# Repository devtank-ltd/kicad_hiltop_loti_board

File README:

Copyright Devtank Ltd 2021.

This documentation describes Open Hardware and is Licensed under CERN-OHL-W v2.

You may redistribute and modify this documentation under the terms of the CERN-OHL-W v2 (https://cern.ch/cern-ohl). This documentation is distributed WITHOUT ANY EXPRESS OR IMPLIED WARRANTY, INCLUDING OF MERCHANTABILITY, SATISFACTORY QUALITY AND FITNESS FOR A PARTICULAR PURPOSE. Please see the CERN-OHL-W v2 for applicable conditions

Source location: git@github.com:devtank-ltd/kicad_hiltop_loti_board.git 

As per CERN-OHL-W v2 section 4.1, should You produce hardware based on these sources, You must maintain the Source Location visible on the external case of the HILTOP or other product you make using this documentation.

This folder contains HILTOP LoTI Board hardware schematics and pcb layout files 

You will need Kicad to open hardware design files.

LoTI Boards and other test and measurement products can be purchased directly from Devtank Ltd.

Please contact:
Tim Telford
CTO - Devtank Ltd
+44 (0)1332 650944

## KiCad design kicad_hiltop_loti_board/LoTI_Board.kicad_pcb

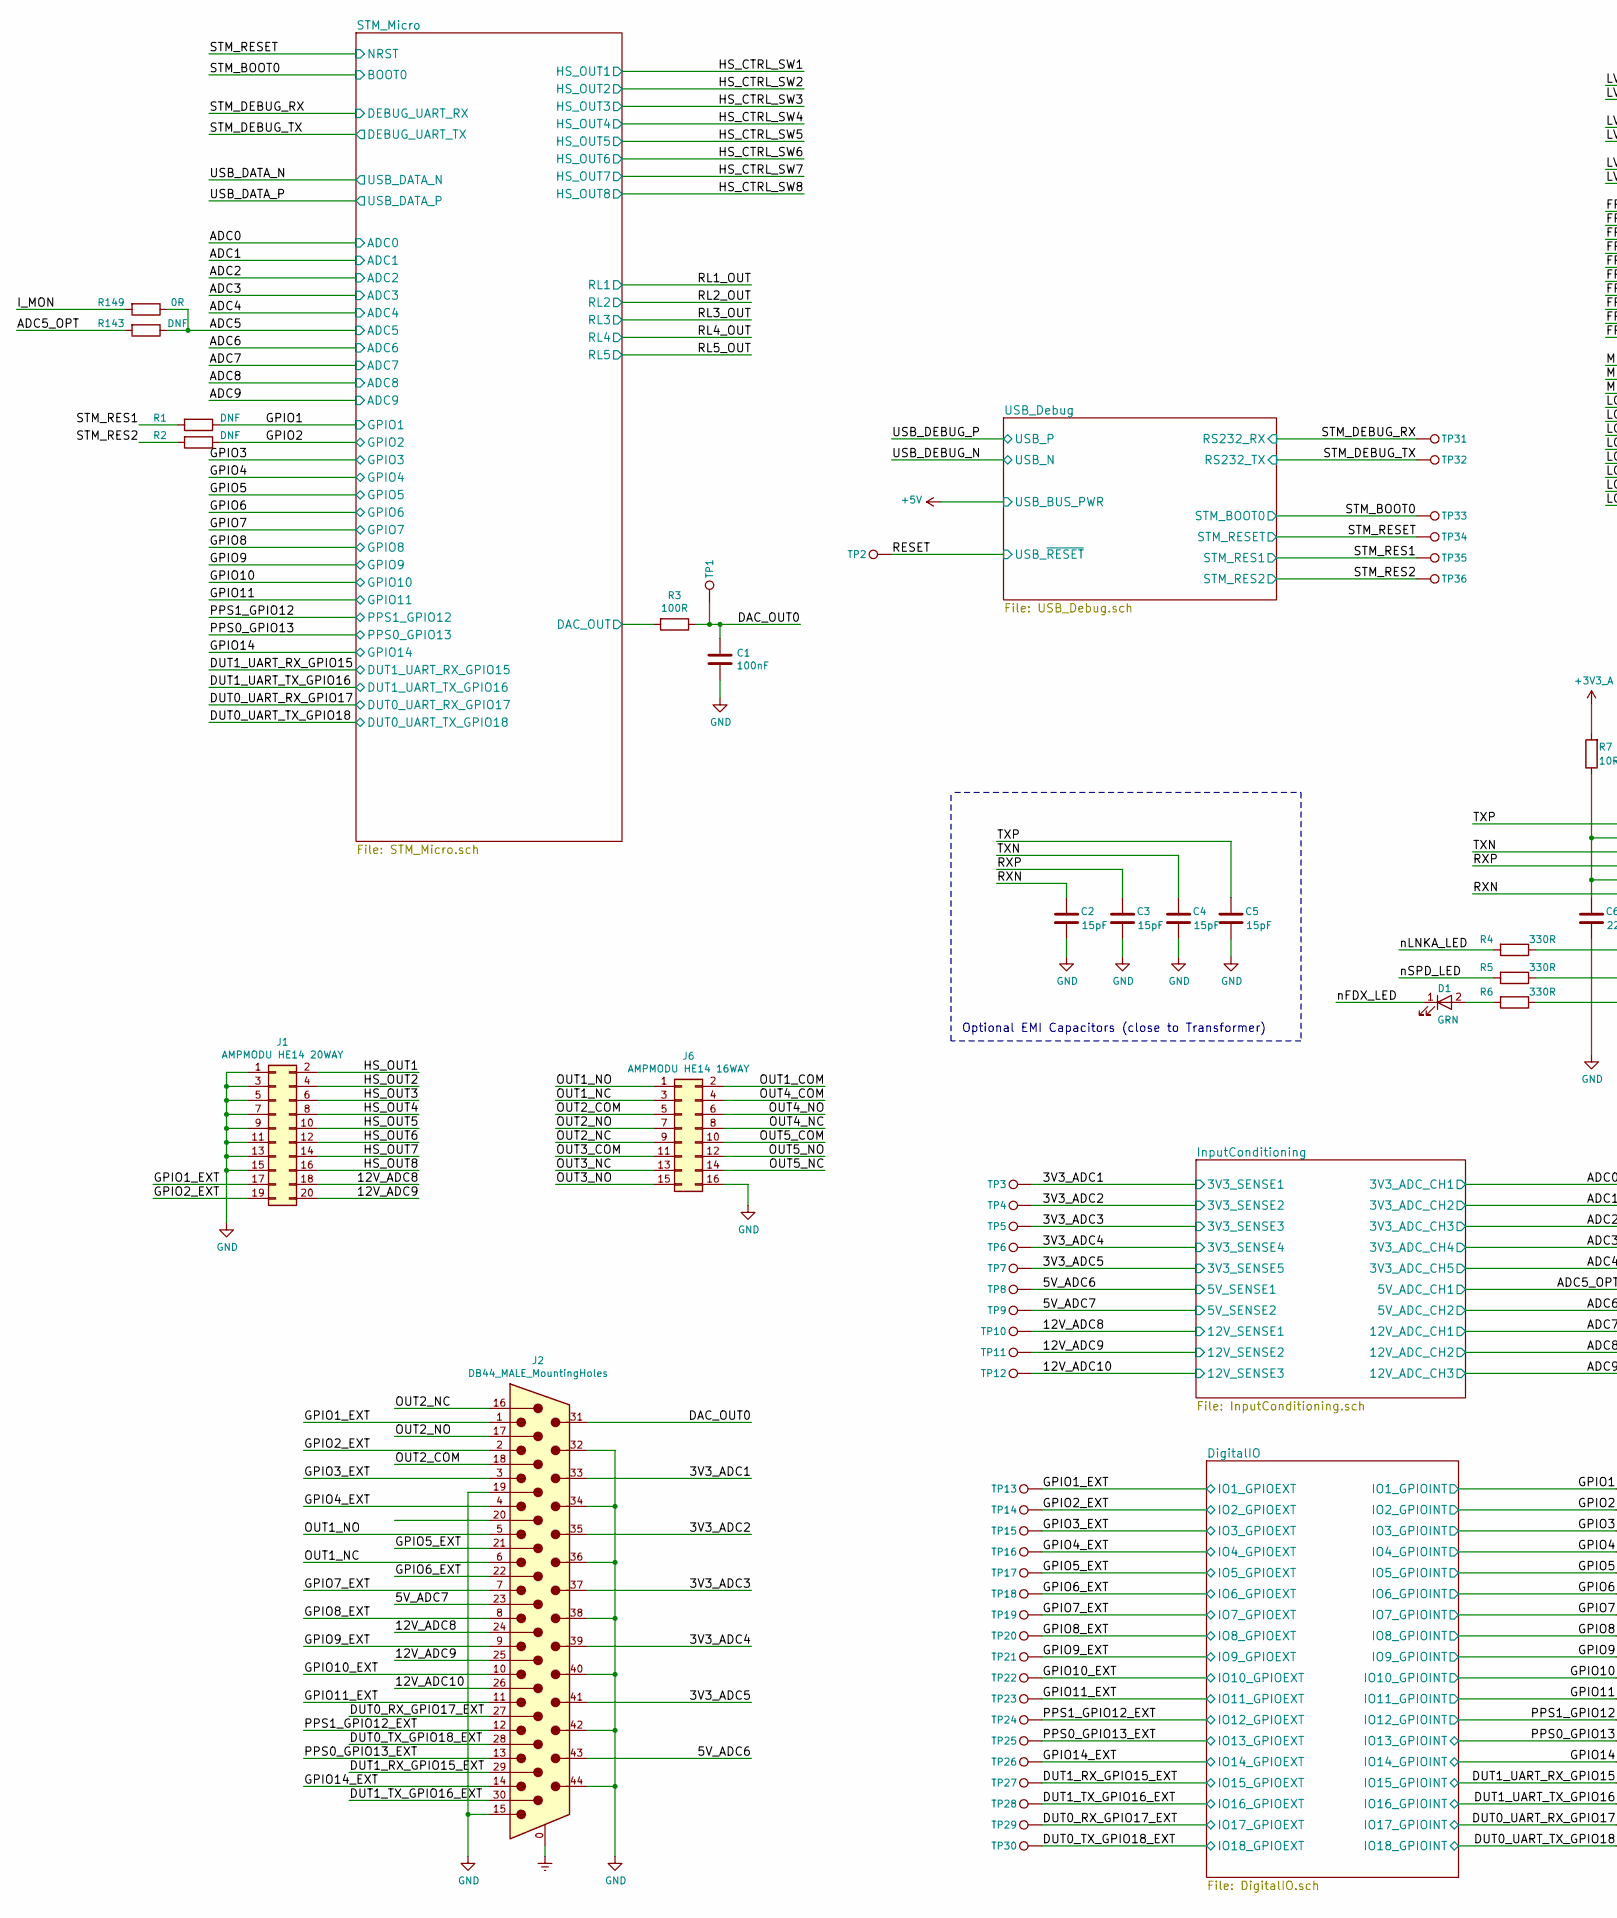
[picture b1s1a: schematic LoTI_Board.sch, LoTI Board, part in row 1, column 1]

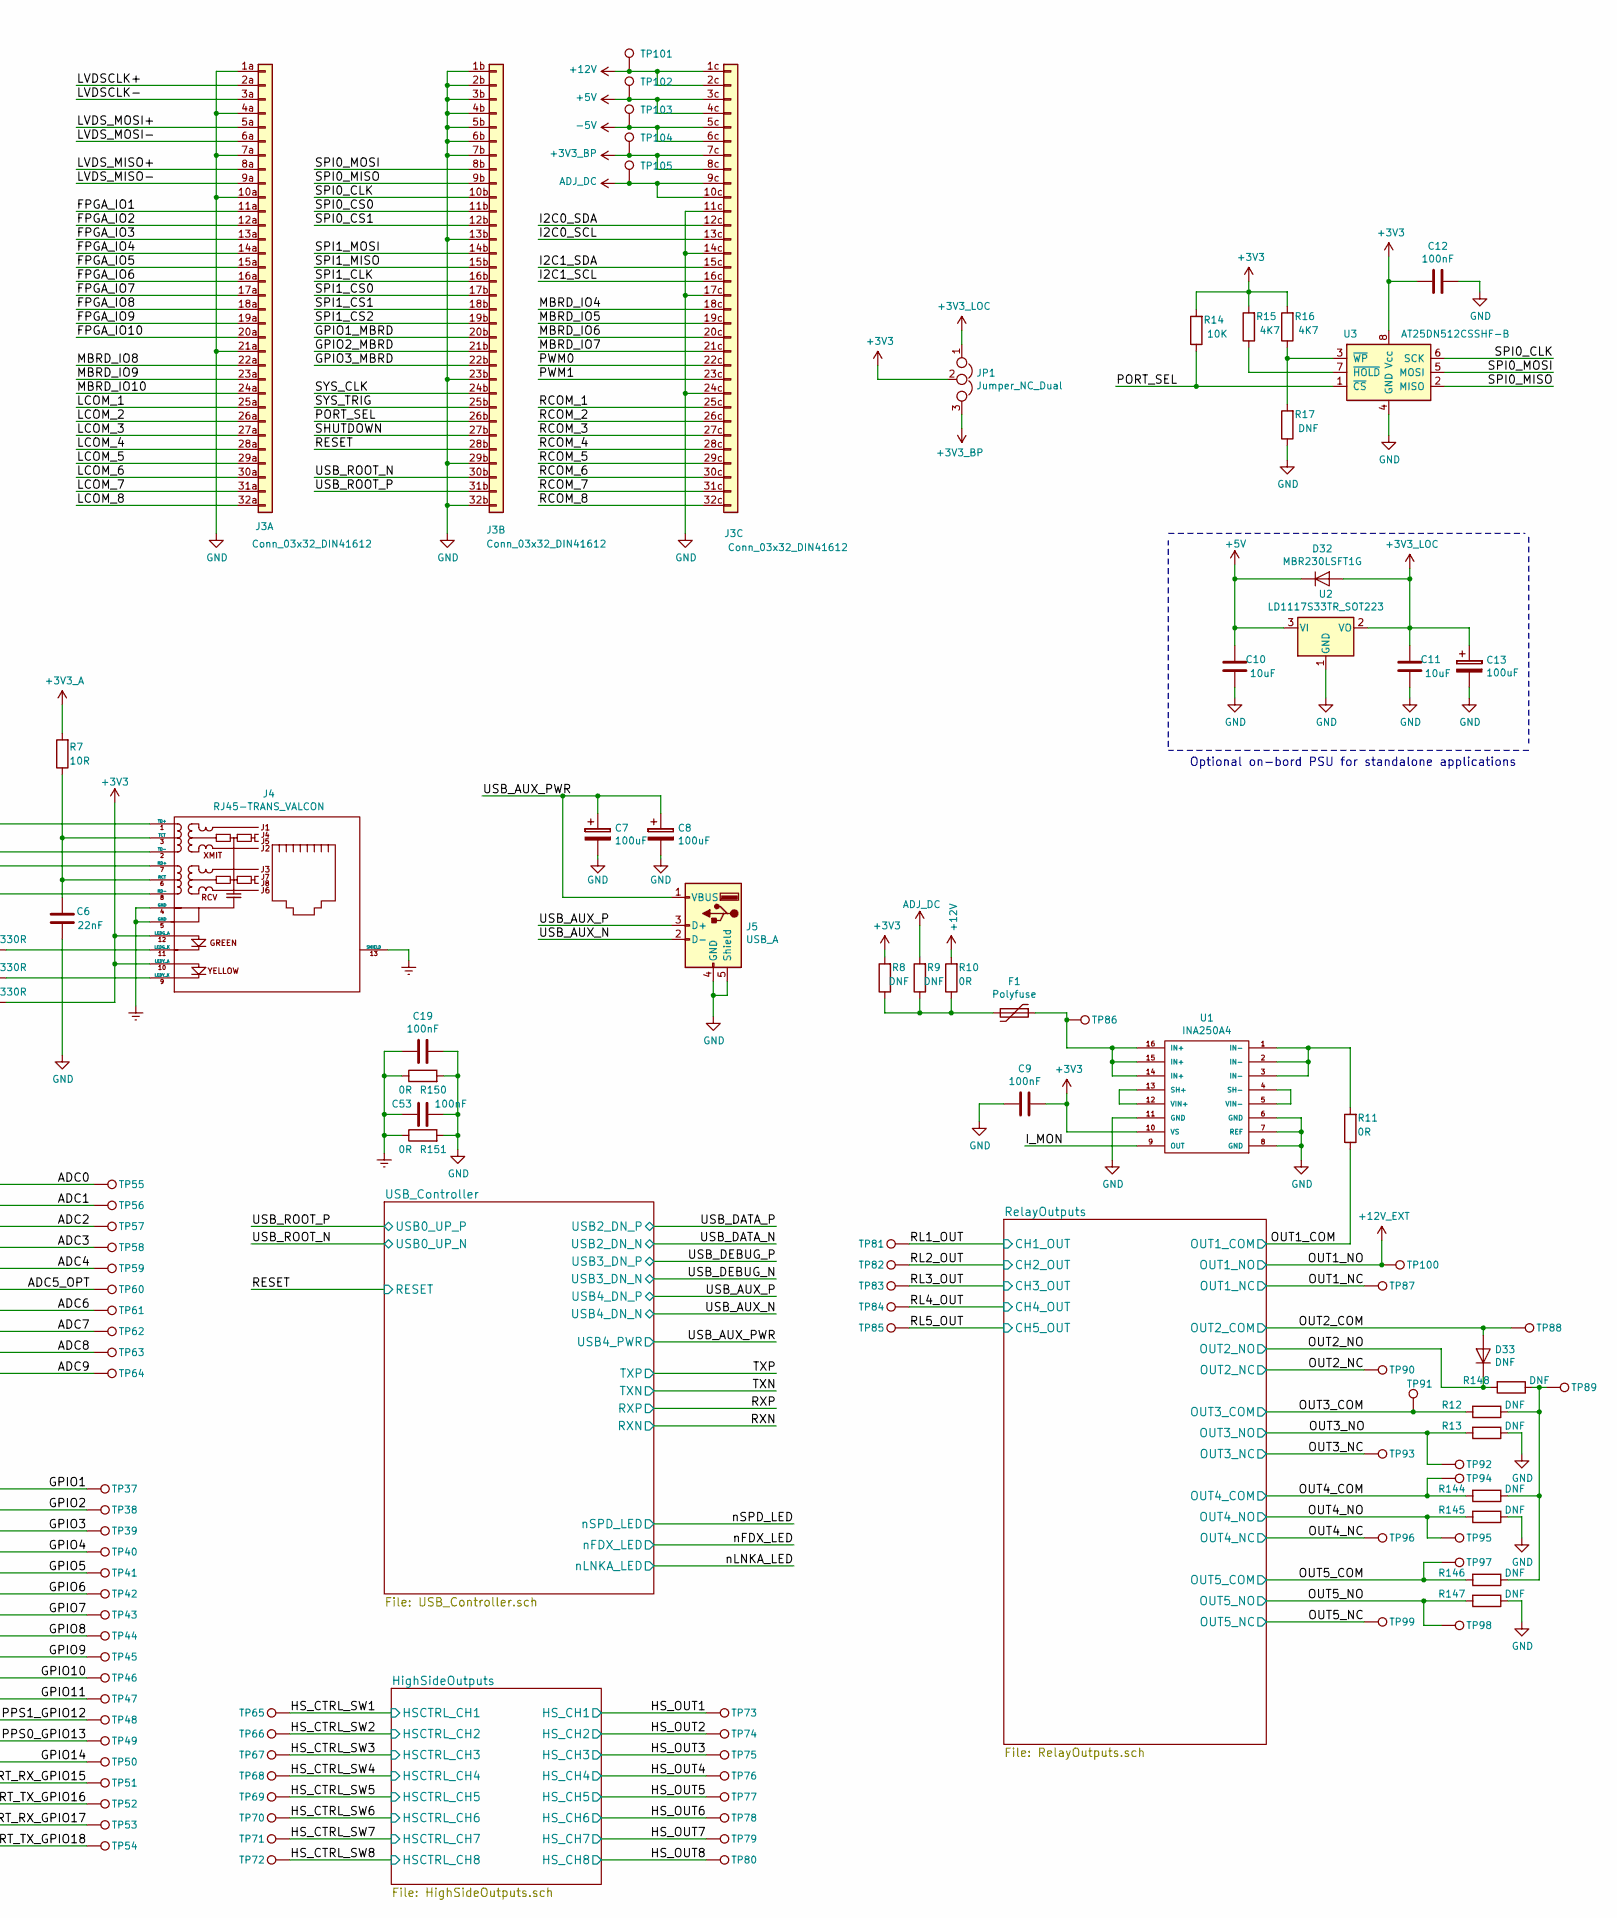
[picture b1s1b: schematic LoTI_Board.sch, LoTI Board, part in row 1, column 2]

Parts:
C1, C9, C12: 100nF; C_0603_1608Metric
C2, C3, C4, C5: 15pF; C_0402_1005Metric
C6: 22nF; R_0603_1608Metric
C7, C8, C13: 100uF; CP_Elec_6.3x7.7
C10, C11: 10uF; C_0805_2012Metric
C19, C53: 100nF; R_1210_3225Metric
D1: GRN; LED_0603_1608Metric
D32: MBR230LSFT1G; D_SOD-123
D33: DNF; D_SOD-123
F1: Polyfuse; R_1206_3216Metric
J1: AMPMODU HE14 20WAY; IDC-Header_2x10_P2.54mm_Vertical
J2: DB44_MALE_MountingHoles; DSUB-44-HD_Female_Horizontal_P2.29x1.98mm_EdgePinOffset8.35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
J3: Conn_03x32_DIN41612; Socket_DIN41612-CaseC1-full-Male-96Pin-3rows_correct
J4: RJ45-TRANS_VALCON; RJ45_TRANSFO_VALCON
J5: USB_A; USB_A_Vertical_Lumberg_2410_01
J6: AMPMODU HE14 16WAY; IDC-Header_2x08_P2.54mm_Vertical
JP1: Jumper_NC_Dual; PinHeader_1x03_P2.54mm_Vertical
R1, R2, R12, R13, R17, R143, R144, R145, R146, R147, R148: DNF; R_0603_1608Metric
R3: 100R; R_0603_1608Metric
R4, R5, R6: 330R; R_0603_1608Metric
R7: 10R; R_0402_1005Metric
R8, R9: DNF; R_1206_3216Metric
R10, R11: 0R; R_1206_3216Metric
R14: 10K; R_0603_1608Metric
R15, R16: 4K7; R_0603_1608Metric
R149: 0R; R_0603_1608Metric
R150, R151: 0R; R_1210_3225Metric
TP1, TP2, TP3, TP4, TP5, TP6, TP7, TP8, TP9, TP10, TP11, TP12, TP13, TP14, TP15, TP16, TP17, TP18, TP19, TP20, TP21, TP22, TP23, TP24, TP25, TP26, TP27, TP28, TP29, TP30, TP31, TP32, TP33, TP34, TP35, TP36, TP37, TP38, TP39, TP40, TP41, TP42, TP43, TP44, TP45, TP46, TP47, TP48, TP49, TP50, TP51, TP52, TP53, TP54, TP55, TP56, TP57, TP58, TP59, TP60, TP61, TP62, TP63, TP64, TP65, TP66, TP67, TP68, TP69, TP70, TP71, TP72, TP73, TP74, TP75, TP76, TP77, TP78, TP79, TP80, TP81, TP82, TP83, TP84, TP85, TP86, TP87, TP88, TP89, TP90, TP91, TP92, TP93, TP94, TP95, TP96, TP97, TP98, TP99, TP100, TP101, TP102, TP103, TP104, TP105: Test_Point; TestPoint_THTPad_D1.0mm_Drill0.5mm
U1: INA250A4; TSSOP-16_4.4x5mm_P0.65mm
U2: LD1117S33TR_SOT223; SOT-223-3_TabPin2
U3: AT25DN512CSSHF-B; SOIC-8_3.9x4.9mm_P1.27mm

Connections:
+3V3: C9.1, C12.2, J4.10 (LEDY_A), J4.12 (LEDG_A), JP1.2, R6.1, R8.2, R14.2, R15.2, R16.2, U1.10 (VS), U3.8 (Vcc); also elsewhere on the board
+3V3_A: R7.2; also elsewhere on the board
+3V3_BP: J3.7c (Pin_7), J3.8c (Pin_8), JP1.3, TP104.1
+3V3_LOC: C11.2, C13.1, D32.2 (A), JP1.1, U2.2 (VO)
+5V: C10.2, D32.1 (K), J3.3c (Pin_3), J3.4c (Pin_4), TP102.1, U2.3 (VI); also elsewhere on the board
+12V: J3.1c (Pin_1), J3.2c (Pin_2), R10.2, TP101.1; also elsewhere on the board
+12V_EXT: J2.5, J6.1, TP100.1; also elsewhere on the board
-5V: J3.5c (Pin_5), J3.6c (Pin_6), TP103.1
/3V3_ADC1: J2.33, TP3.1; also elsewhere on the board
/3V3_ADC2: J2.35, TP4.1; also elsewhere on the board
/3V3_ADC3: J2.37, TP5.1; also elsewhere on the board
/3V3_ADC4: J2.39, TP6.1; also elsewhere on the board
/3V3_ADC5: J2.41, TP7.1; also elsewhere on the board
/5V_ADC6: J2.43, TP8.1; also elsewhere on the board
/5V_ADC7: J2.23, TP9.1; also elsewhere on the board
/12V_ADC8: J1.18, J2.24, TP10.1; also elsewhere on the board
/12V_ADC9: J1.20, J2.25, TP11.1; also elsewhere on the board
/12V_ADC10: J2.26, TP12.1; also elsewhere on the board
/ADC0: TP55.1; also elsewhere on the board
/ADC1: TP56.1; also elsewhere on the board
/ADC2: TP57.1; also elsewhere on the board
/ADC3: TP58.1; also elsewhere on the board
/ADC4: TP59.1; also elsewhere on the board
/ADC5: R143.1, R149.1; also elsewhere on the board
/ADC5_OPT: R143.2, TP60.1; also elsewhere on the board
/ADC6: TP61.1; also elsewhere on the board
/ADC7: TP62.1; also elsewhere on the board
/ADC8: TP63.1; also elsewhere on the board
/ADC9: TP64.1; also elsewhere on the board
/DAC_OUT0: C1.1, J2.31, R3.1, TP1.1
/DUT0_RX_GPIO17_EXT: J2.27, TP29.1; also elsewhere on the board
/DUT0_TX_GPIO18_EXT: J2.28, TP30.1; also elsewhere on the board
/DUT0_UART_RX_GPIO17: TP53.1; also elsewhere on the board
/DUT0_UART_TX_GPIO18: TP54.1; also elsewhere on the board
/DUT1_RX_GPIO15_EXT: J2.29, TP27.1; also elsewhere on the board
/DUT1_TX_GPIO16_EXT: J2.30, TP28.1; also elsewhere on the board
/DUT1_UART_RX_GPIO15: TP51.1; also elsewhere on the board
/DUT1_UART_TX_GPIO16: TP52.1; also elsewhere on the board
/FPGA_IO1: J3.11a (Pin_11)
/FPGA_IO2: J3.12a (Pin_12)
/FPGA_IO3: J3.13a (Pin_13)
/FPGA_IO4: J3.14a (Pin_14)
/FPGA_IO5: J3.15a (Pin_15)
/FPGA_IO6: J3.16a (Pin_16)
/FPGA_IO7: J3.17a (Pin_17)
/FPGA_IO8: J3.18a (Pin_18)
/FPGA_IO9: J3.19a (Pin_19)
/FPGA_IO10: J3.20a (Pin_20)
/GPIO1: R1.1, TP37.1; also elsewhere on the board
/GPIO1_EXT: J1.17, J2.1, TP13.1; also elsewhere on the board
/GPIO1_MBRD: J3.20b (Pin_20)
/GPIO2: R2.1, TP38.1; also elsewhere on the board
/GPIO2_EXT: J1.19, J2.2, TP14.1; also elsewhere on the board
/GPIO2_MBRD: J3.21b (Pin_21)
/GPIO3: TP39.1; also elsewhere on the board
/GPIO3_EXT: J2.3, TP15.1; also elsewhere on the board
/GPIO3_MBRD: J3.22b (Pin_22)
/GPIO4: TP40.1; also elsewhere on the board
/GPIO4_EXT: J2.4, TP16.1; also elsewhere on the board
/GPIO5: TP41.1; also elsewhere on the board
/GPIO5_EXT: J2.21, TP17.1; also elsewhere on the board
/GPIO6: TP42.1; also elsewhere on the board
/GPIO6_EXT: J2.22, TP18.1; also elsewhere on the board
/GPIO7: TP43.1; also elsewhere on the board
/GPIO7_EXT: J2.7, TP19.1; also elsewhere on the board
/GPIO8: TP44.1; also elsewhere on the board
/GPIO8_EXT: J2.8, TP20.1; also elsewhere on the board
/GPIO9: TP45.1; also elsewhere on the board
/GPIO9_EXT: J2.9, TP21.1; also elsewhere on the board
/GPIO10: TP46.1; also elsewhere on the board
/GPIO10_EXT: J2.10, TP22.1; also elsewhere on the board
/GPIO11: TP47.1; also elsewhere on the board
/GPIO11_EXT: J2.11, TP23.1; also elsewhere on the board
/GPIO14: TP50.1; also elsewhere on the board
/GPIO14_EXT: J2.14, TP26.1; also elsewhere on the board
/HS_CTRL_SW1: TP65.1; also elsewhere on the board
/HS_CTRL_SW2: TP66.1; also elsewhere on the board
/HS_CTRL_SW3: TP67.1; also elsewhere on the board
/HS_CTRL_SW4: TP68.1; also elsewhere on the board
/HS_CTRL_SW5: TP69.1; also elsewhere on the board
/HS_CTRL_SW6: TP70.1; also elsewhere on the board
/HS_CTRL_SW7: TP71.1; also elsewhere on the board
/HS_CTRL_SW8: TP72.1; also elsewhere on the board
/HS_OUT1: J1.2, TP73.1; also elsewhere on the board
/HS_OUT2: J1.4, TP74.1; also elsewhere on the board
/HS_OUT3: J1.6, TP75.1; also elsewhere on the board
/HS_OUT4: J1.8, TP76.1; also elsewhere on the board
/HS_OUT5: J1.10, TP77.1; also elsewhere on the board
/HS_OUT6: J1.12, TP78.1; also elsewhere on the board
/HS_OUT7: J1.14, TP79.1; also elsewhere on the board
/HS_OUT8: J1.16, TP80.1; also elsewhere on the board
/I2C0_SCL: J3.13c (Pin_13)
/I2C0_SDA: J3.12c (Pin_12)
/I2C1_SCL: J3.16c (Pin_16)
/I2C1_SDA: J3.15c (Pin_15)
/I_MON: R149.2, U1.9 (OUT)
/LCOM_1: J3.25a (Pin_25)
/LCOM_2: J3.26a (Pin_26)
/LCOM_3: J3.27a (Pin_27)
/LCOM_4: J3.28a (Pin_28)
/LCOM_5: J3.29a (Pin_29)
/LCOM_6: J3.30a (Pin_30)
/LCOM_7: J3.31a (Pin_31)
/LCOM_8: J3.32a (Pin_32)
/LVDSCLK+: J3.2a (Pin_2)
/LVDSCLK-: J3.3a (Pin_3)
/LVDS_MISO+: J3.8a (Pin_8)
/LVDS_MISO-: J3.9a (Pin_9)
/LVDS_MOSI+: J3.5a (Pin_5)
/LVDS_MOSI-: J3.6a (Pin_6)
/MBRD_IO4: J3.18c (Pin_18)
/MBRD_IO5: J3.19c (Pin_19)
/MBRD_IO6: J3.20c (Pin_20)
/MBRD_IO7: J3.21c (Pin_21)
/MBRD_IO8: J3.22a (Pin_22)
/MBRD_IO9: J3.23a (Pin_23)
/MBRD_IO10: J3.24a (Pin_24)
/OUT1_COM: J6.2, R11.1; also elsewhere on the board
/OUT1_NC: J2.6, J6.3, TP87.1; also elsewhere on the board
/OUT2_COM: D33.2 (A), J2.18, J6.5, TP88.1; also elsewhere on the board
/OUT2_NC: J2.16, J6.9, TP90.1; also elsewhere on the board
/OUT2_NO: D33.1 (K), J2.17, J6.7, R148.2; also elsewhere on the board
/OUT3_COM: J6.11, R12.2, TP91.1; also elsewhere on the board
/OUT3_NC: J6.13, TP93.1; also elsewhere on the board
/OUT3_NO: J6.15, R13.2, TP92.1; also elsewhere on the board
/OUT4_COM: J6.4, R144.2, TP94.1; also elsewhere on the board
/OUT4_NC: J6.8, TP96.1; also elsewhere on the board
/OUT4_NO: J6.6, R145.2, TP95.1; also elsewhere on the board
/OUT5_COM: J6.10, R146.2, TP97.1; also elsewhere on the board
/OUT5_NC: J6.14, TP99.1; also elsewhere on the board
/OUT5_NO: J6.12, R147.2, TP98.1; also elsewhere on the board
/PORT_SEL: J3.26b (Pin_26), R14.1, U3.1 (~CS)
/PPS0_GPIO13: TP49.1; also elsewhere on the board
/PPS0_GPIO13_EXT: J2.13, TP25.1; also elsewhere on the board
/PPS1_GPIO12: TP48.1; also elsewhere on the board
/PPS1_GPIO12_EXT: J2.12, TP24.1; also elsewhere on the board
/PWM0: J3.22c (Pin_22)
/PWM1: J3.23c (Pin_23)
/RCOM_1: J3.25c (Pin_25)
/RCOM_2: J3.26c (Pin_26)
/RCOM_3: J3.27c (Pin_27)
/RCOM_4: J3.28c (Pin_28)
/RCOM_5: J3.29c (Pin_29)
/RCOM_6: J3.30c (Pin_30)
/RCOM_7: J3.31c (Pin_31)
/RCOM_8: J3.32c (Pin_32)
/RESET: J3.28b (Pin_28), TP2.1; also elsewhere on the board
/RL1_OUT: TP81.1; also elsewhere on the board
/RL2_OUT: TP82.1; also elsewhere on the board
/RL3_OUT: TP83.1; also elsewhere on the board
/RL4_OUT: TP84.1; also elsewhere on the board
/RL5_OUT: TP85.1; also elsewhere on the board
/RXN: C2.2, J4.8 (RD-); also elsewhere on the board
/RXP: C3.2, J4.7 (RD+); also elsewhere on the board
/SHUTDOWN: J3.27b (Pin_27)
/SPI0_CLK: J3.10b (Pin_10), U3.6 (SCK)
/SPI0_CS0: J3.11b (Pin_11)
/SPI0_CS1: J3.12b (Pin_12)
/SPI0_MISO: J3.9b (Pin_9), U3.2 (MISO)
/SPI0_MOSI: J3.8b (Pin_8), U3.5 (MOSI)
/SPI1_CLK: J3.16b (Pin_16)
/SPI1_CS0: J3.17b (Pin_17)
/SPI1_CS1: J3.18b (Pin_18)
/SPI1_CS2: J3.19b (Pin_19)
/SPI1_MISO: J3.15b (Pin_15)
/SPI1_MOSI: J3.14b (Pin_14)
/STM_BOOT0: TP33.1; also elsewhere on the board
/STM_DEBUG_RX: TP31.1; also elsewhere on the board
/STM_DEBUG_TX: TP32.1; also elsewhere on the board
/STM_Micro/DAC_OUT: R3.2; also elsewhere on the board
/STM_RES1: R1.2, TP35.1; also elsewhere on the board
/STM_RES2: R2.2, TP36.1; also elsewhere on the board
/STM_RESET: TP34.1; also elsewhere on the board
/SYS_CLK: J3.24b (Pin_24)
/SYS_TRIG: J3.25b (Pin_25)
/TXN: C4.2, J4.2 (TD-); also elsewhere on the board
/TXP: C5.2, J4.1 (TD+); also elsewhere on the board
/USB_AUX_N: J5.2 (D-); also elsewhere on the board
/USB_AUX_P: J5.3 (D+); also elsewhere on the board
/USB_AUX_PWR: C7.1, C8.1, J5.1 (VBUS); also elsewhere on the board
/USB_ROOT_N: J3.30b (Pin_30); also elsewhere on the board
/USB_ROOT_P: J3.31b (Pin_31); also elsewhere on the board
/nFDX_LED: D1.1 (K); also elsewhere on the board
/nLNKA_LED: R4.2; also elsewhere on the board
/nSPD_LED: R5.2; also elsewhere on the board
ADJ_DC: J3.9c (Pin_9), J3.10c (Pin_10), R9.2, TP105.1; also elsewhere on the board
Earth: C19.2, C53.2, J2.0 (PAD), J4.4 (GND), J4.5 (GND), J4.13 (SHIELD), R150.1, R151.1
GND: C1.2, C2.1, C3.1, C4.1, C5.1, C6.1, C7.2, C8.2, C9.2, C10.1, C11.1, C12.1, C13.2, C19.1, C53.1, J1.1, J1.3, J1.5, J1.7, J1.9, J1.11, J1.13, J1.15, J2.15, J2.19, J2.32, J2.34, J2.36, J2.38, J2.40, J2.42, J2.44, J3.1a (Pin_1), J3.1b (Pin_1), J3.2b (Pin_2), J3.3b (Pin_3), J3.4a (Pin_4), J3.4b (Pin_4), J3.5b (Pin_5), J3.6b (Pin_6), J3.7a (Pin_7), J3.7b (Pin_7), J3.10a (Pin_10), J3.11c (Pin_11), J3.13b (Pin_13), J3.14c (Pin_14), J3.17c (Pin_17), J3.21a (Pin_21), J3.23b (Pin_23), J3.24c (Pin_24), J3.29b (Pin_29), J3.32b (Pin_32), J5.4 (GND), J5.5 (Shield), J6.16, R13.1, R17.1, R145.1, R147.1, R150.2, R151.2, U1.6 (GND), U1.7 (REF), U1.8 (GND), U1.11 (GND), U2.1 (GND), U3.4 (GND); also elsewhere on the board
unnamed: C6.2, J4.3 (TCT), J4.6 (RCT), R7.1
unnamed: D1.2 (A), R6.2
unnamed: F1.1, TP86.1, U1.14 (IN+), U1.15 (IN+), U1.16 (IN+)
unnamed: F1.2, R8.1, R9.1, R10.1
unnamed: J4.9 (LEDY_K), R5.1
unnamed: J4.11 (LEDG_K), R4.1
unnamed: R11.2, U1.1 (IN-), U1.2 (IN-), U1.3 (IN-)
unnamed: R12.1, R144.1, R146.1, R148.1, TP89.1
unnamed: R15.1, U3.7 (~HOLD)
unnamed: R16.1, R17.2, U3.3 (~WP)
unnamed: U1.4 (SH-), U1.5 (VIN-)
unnamed: U1.12 (VIN+), U1.13 (SH+)

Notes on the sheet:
Optional EMI Capacitors (close to Transformer)
Optional on-bord PSU for standalone applications

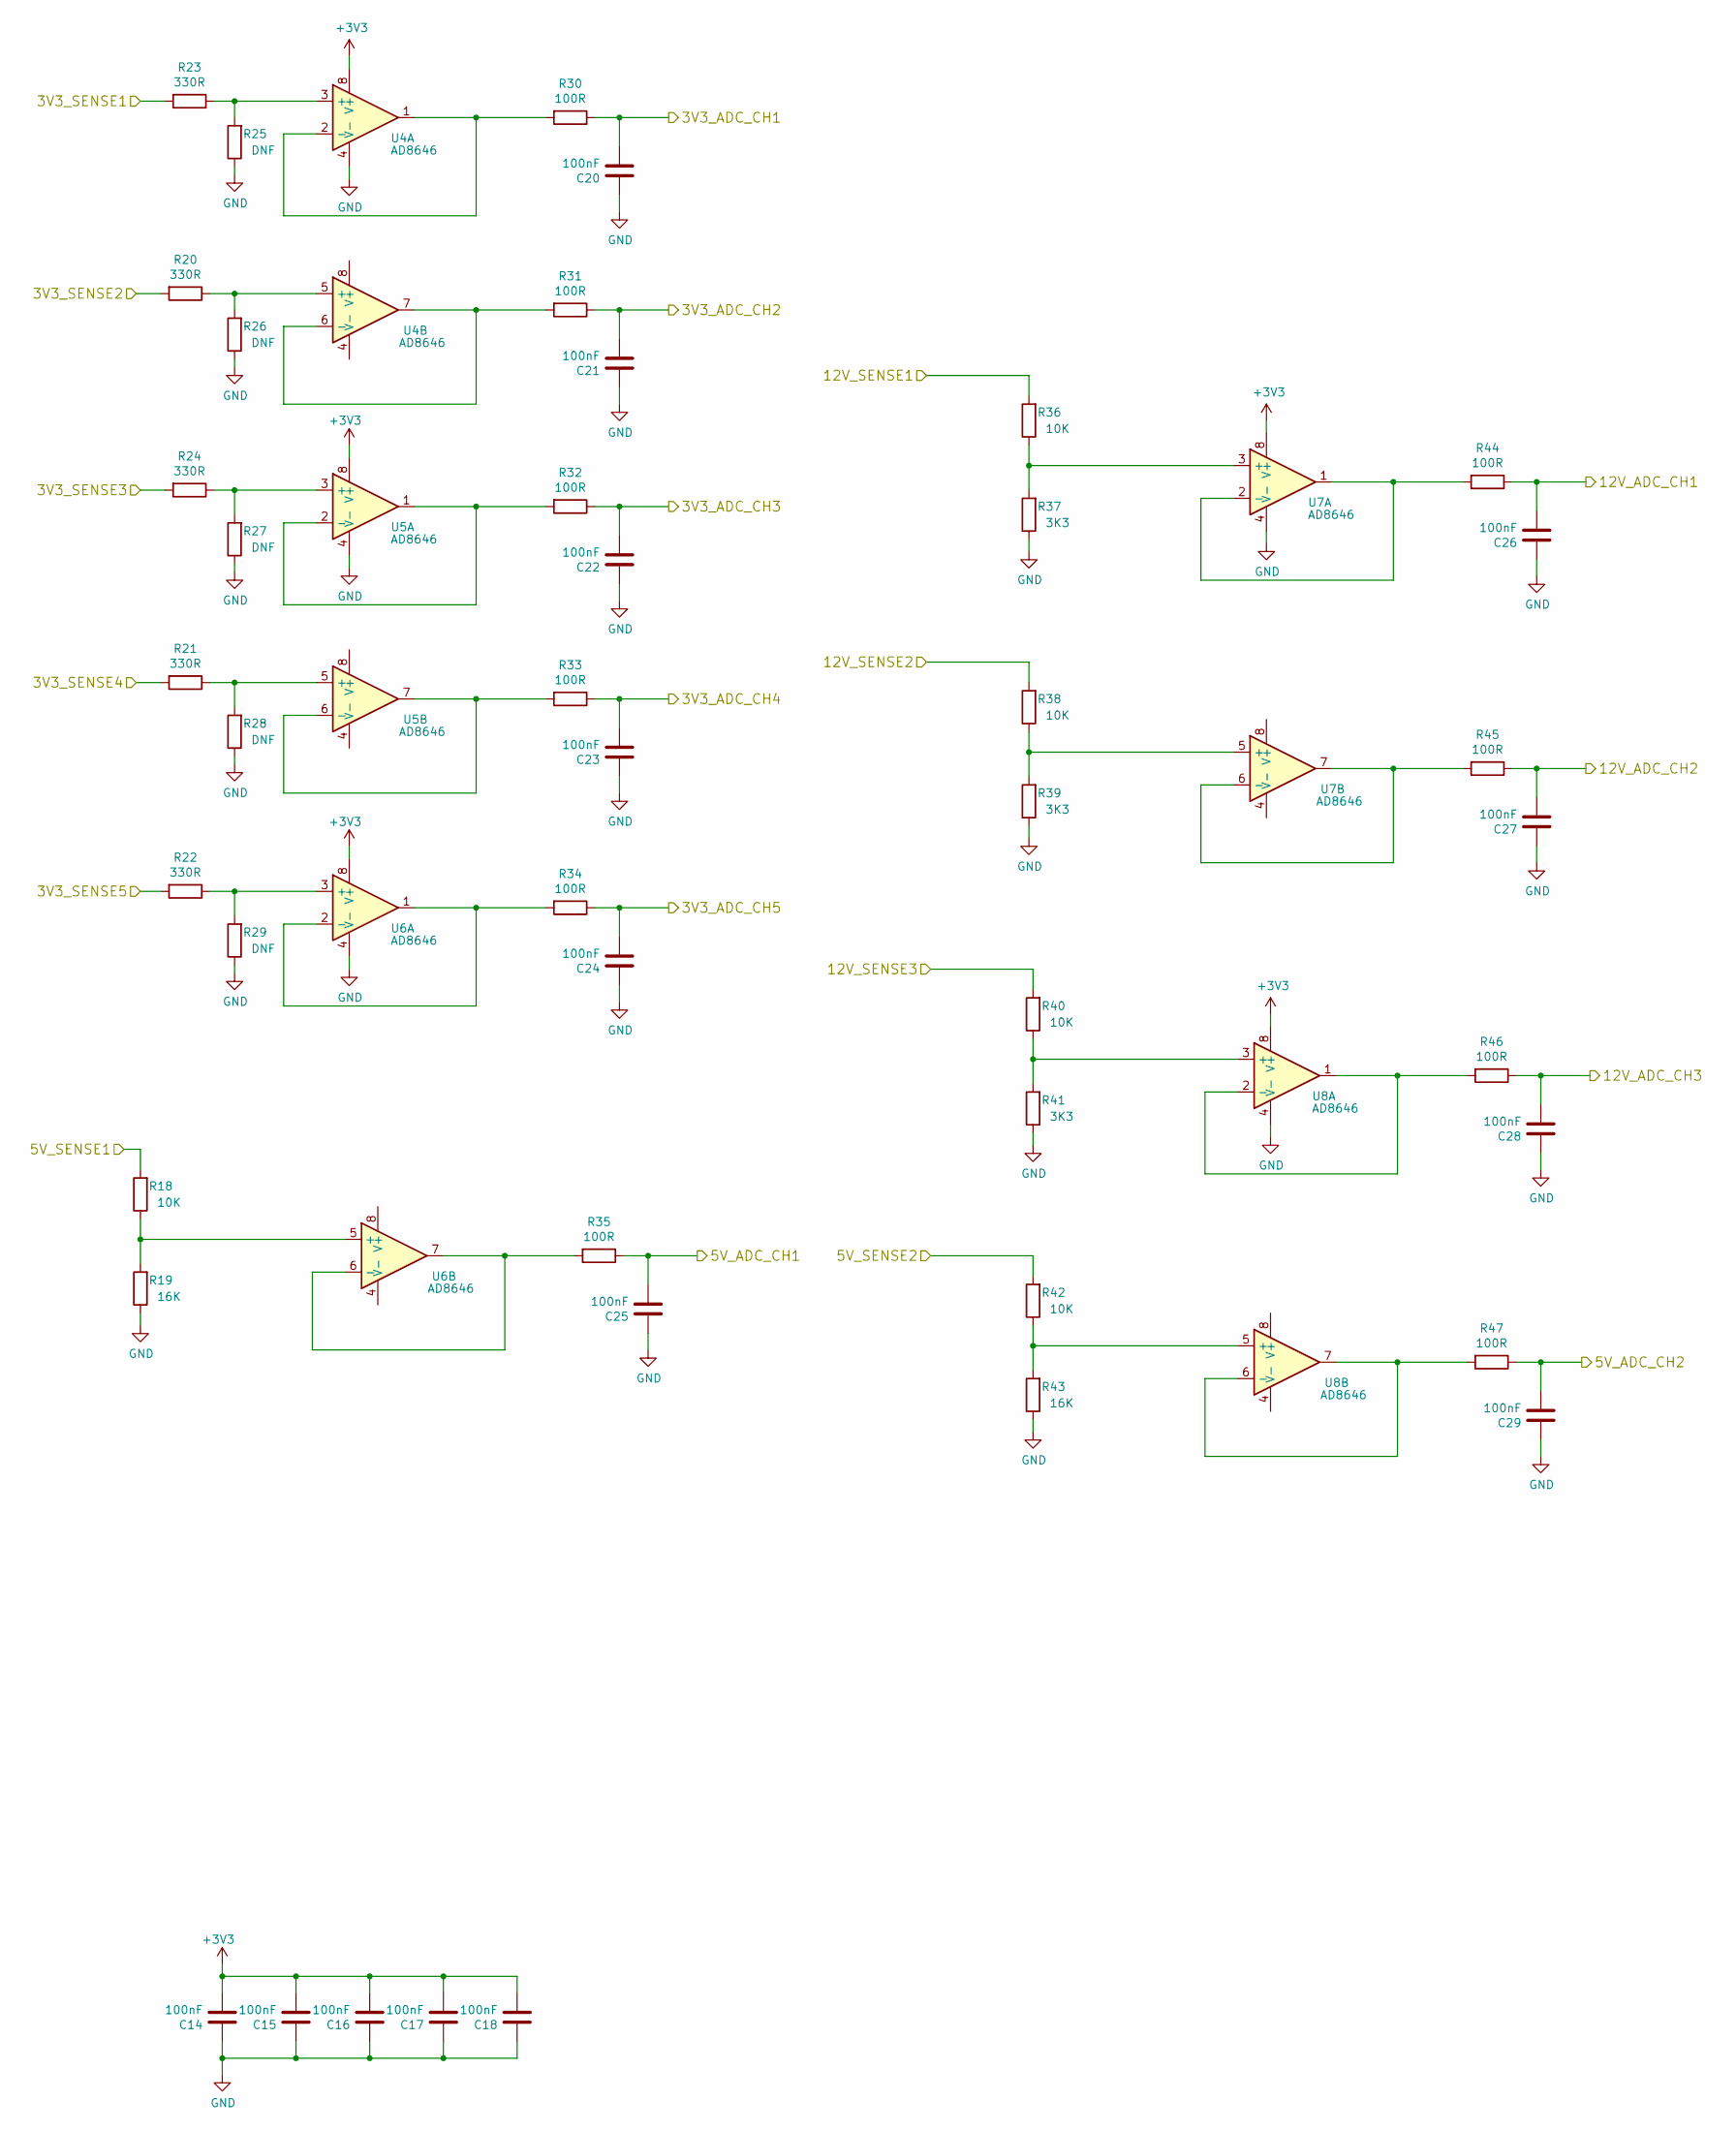
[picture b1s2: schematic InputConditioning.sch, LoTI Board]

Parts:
C14, C15, C16, C17, C18, C20, C21, C22, C23, C24, C25, C26, C27, C28, C29: 100nF; C_0603_1608Metric
R18, R36, R38, R40, R42: 10K; R_0603_1608Metric
R19, R43: 16K; R_0603_1608Metric
R20, R21, R22, R23, R24: 330R; R_0603_1608Metric
R25, R26, R27, R28, R29: DNF; R_0603_1608Metric
R30, R31, R32, R33, R34, R35, R44, R45, R46, R47: 100R; R_0603_1608Metric
R37, R39, R41: 3K3; R_0603_1608Metric
U4, U5, U6, U7, U8: AD8646; SOIC-8_3.9x4.9mm_P1.27mm

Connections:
+3V3: C14.2, C15.2, C16.2, C17.2, C18.2, U4.8 (V+), U5.8 (V+), U6.8 (V+), U7.8 (V+), U8.8 (V+); also elsewhere on the board
/3V3_ADC1: R23.2; also elsewhere on the board
/3V3_ADC2: R20.2; also elsewhere on the board
/3V3_ADC3: R24.2; also elsewhere on the board
/3V3_ADC4: R21.2; also elsewhere on the board
/3V3_ADC5: R22.2; also elsewhere on the board
/5V_ADC6: R18.2; also elsewhere on the board
/5V_ADC7: R42.2; also elsewhere on the board
/12V_ADC8: R36.2; also elsewhere on the board
/12V_ADC9: R38.2; also elsewhere on the board
/12V_ADC10: R40.2; also elsewhere on the board
/ADC0: C20.2, R30.1; also elsewhere on the board
/ADC1: C21.2, R31.1; also elsewhere on the board
/ADC2: C22.2, R32.1; also elsewhere on the board
/ADC3: C23.2, R33.1; also elsewhere on the board
/ADC4: C24.2, R34.1; also elsewhere on the board
/ADC5_OPT: C25.2, R35.1; also elsewhere on the board
/ADC6: C29.2, R47.1; also elsewhere on the board
/ADC7: C26.2, R44.1; also elsewhere on the board
/ADC8: C27.2, R45.1; also elsewhere on the board
/ADC9: C28.2, R46.1; also elsewhere on the board
GND: C14.1, C15.1, C16.1, C17.1, C18.1, C20.1, C21.1, C22.1, C23.1, C24.1, C25.1, C26.1, C27.1, C28.1, C29.1, R19.1, R25.1, R26.1, R27.1, R28.1, R29.1, R37.1, R39.1, R41.1, R43.1, U4.4 (V-), U5.4 (V-), U6.4 (V-), U7.4 (V-), U8.4 (V-); also elsewhere on the board
unnamed: R18.1, R19.2, U6.5 (+)
unnamed: R20.1, R26.2, U4.5 (+)
unnamed: R21.1, R28.2, U5.5 (+)
unnamed: R22.1, R29.2, U6.3 (+)
unnamed: R23.1, R25.2, U4.3 (+)
unnamed: R24.1, R27.2, U5.3 (+)
unnamed: R30.2, U4.1, U4.2 (-)
unnamed: R31.2, U4.6 (-), U4.7
unnamed: R32.2, U5.1, U5.2 (-)
unnamed: R33.2, U5.6 (-), U5.7
unnamed: R34.2, U6.1, U6.2 (-)
unnamed: R35.2, U6.6 (-), U6.7
unnamed: R36.1, R37.2, U7.3 (+)
unnamed: R38.1, R39.2, U7.5 (+)
unnamed: R40.1, R41.2, U8.3 (+)
unnamed: R42.1, R43.2, U8.5 (+)
unnamed: R44.2, U7.1, U7.2 (-)
unnamed: R45.2, U7.6 (-), U7.7
unnamed: R46.2, U8.1, U8.2 (-)
unnamed: R47.2, U8.6 (-), U8.7

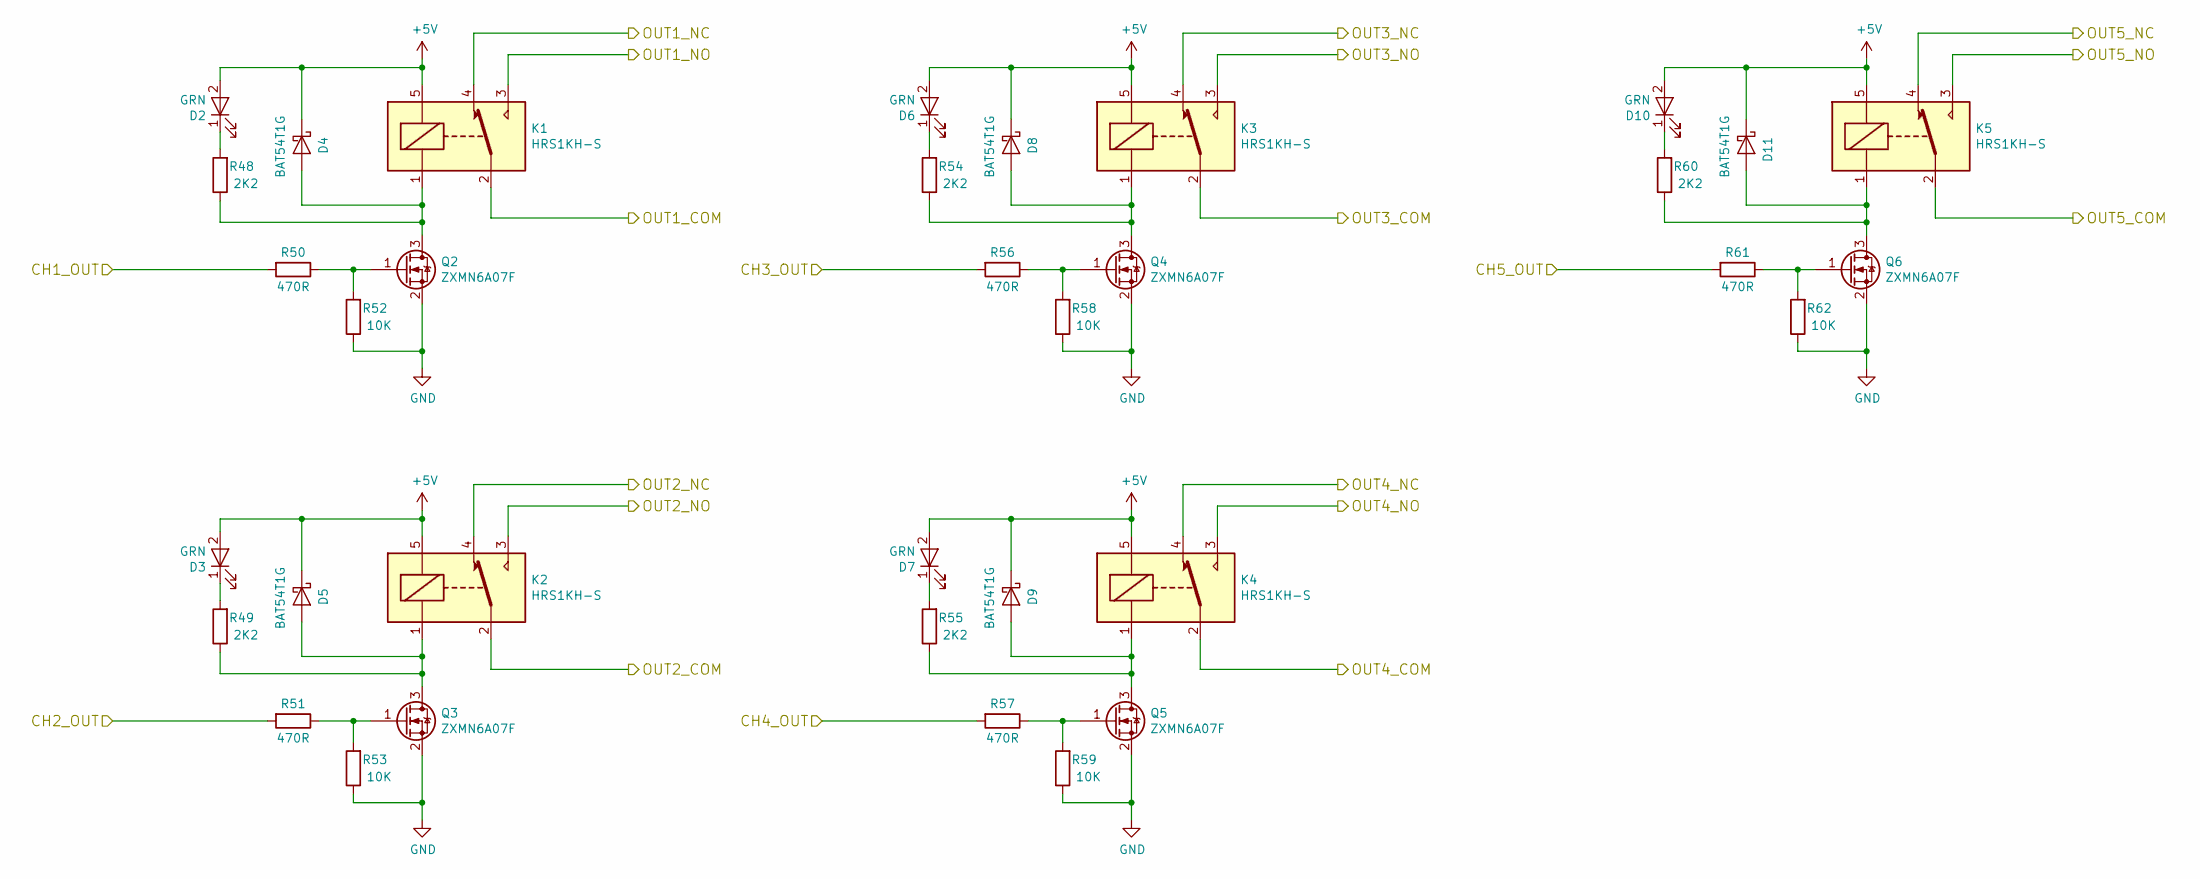
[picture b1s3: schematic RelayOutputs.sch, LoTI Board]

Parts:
D2, D3, D6, D7, D10: GRN; LED_0603_1608Metric
D4, D5, D8, D9, D11: BAT54T1G; D_SOD-123
K1, K2, K3, K4, K5: HRS1KH-S; Relay_SPDT_HRS1KH-S
Q2, Q3, Q4, Q5, Q6: ZXMN6A07F; SOT-23
R48, R49, R54, R55, R60: 2K2; R_0603_1608Metric
R50, R51, R56, R57, R61: 470R; R_0603_1608Metric
R52, R53, R58, R59, R62: 10K; R_0603_1608Metric

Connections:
+5V: D2.2 (A), D3.2 (A), D4.1 (K), D5.1 (K), D6.2 (A), D7.2 (A), D8.1 (K), D9.1 (K), D10.2 (A), D11.1 (K), K1.5, K2.5, K3.5, K4.5, K5.5; also elsewhere on the board
+12V_EXT: K1.3; also elsewhere on the board
/OUT1_COM: K1.2; also elsewhere on the board
/OUT1_NC: K1.4; also elsewhere on the board
/OUT2_COM: K2.2; also elsewhere on the board
/OUT2_NC: K2.4; also elsewhere on the board
/OUT2_NO: K2.3; also elsewhere on the board
/OUT3_COM: K3.2; also elsewhere on the board
/OUT3_NC: K3.4; also elsewhere on the board
/OUT3_NO: K3.3; also elsewhere on the board
/OUT4_COM: K4.2; also elsewhere on the board
/OUT4_NC: K4.4; also elsewhere on the board
/OUT4_NO: K4.3; also elsewhere on the board
/OUT5_COM: K5.2; also elsewhere on the board
/OUT5_NC: K5.4; also elsewhere on the board
/OUT5_NO: K5.3; also elsewhere on the board
/RL1_OUT: R50.2; also elsewhere on the board
/RL2_OUT: R51.2; also elsewhere on the board
/RL3_OUT: R56.2; also elsewhere on the board
/RL4_OUT: R57.2; also elsewhere on the board
/RL5_OUT: R61.2; also elsewhere on the board
GND: Q2.2 (S), Q3.2 (S), Q4.2 (S), Q5.2 (S), Q6.2 (S), R52.1, R53.1, R58.1, R59.1, R62.1; also elsewhere on the board
unnamed: D2.1 (K), R48.2
unnamed: D3.1 (K), R49.2
unnamed: D4.2 (A), K1.1, Q2.3 (D), R48.1
unnamed: D5.2 (A), K2.1, Q3.3 (D), R49.1
unnamed: D6.1 (K), R54.2
unnamed: D7.1 (K), R55.2
unnamed: D8.2 (A), K3.1, Q4.3 (D), R54.1
unnamed: D9.2 (A), K4.1, Q5.3 (D), R55.1
unnamed: D10.1 (K), R60.2
unnamed: D11.2 (A), K5.1, Q6.3 (D), R60.1
unnamed: Q2.1 (G), R50.1, R52.2
unnamed: Q3.1 (G), R51.1, R53.2
unnamed: Q4.1 (G), R56.1, R58.2
unnamed: Q5.1 (G), R57.1, R59.2
unnamed: Q6.1 (G), R61.1, R62.2

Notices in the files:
kicad_hiltop_loti_board/LoTI_Board.kicad_pcb:
(c) Copyright 2021 Devtank Ltd
Licensed under CERN-OHL-W V2.0
https://cern-ohl.web.cern.ch
